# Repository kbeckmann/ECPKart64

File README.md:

# ECPKart64

A Lattice ECP5 based FPGA Flash Cart for the Nintendo 64

## Build and load over serial

```

# First install FPGA toolchain and LiteX

# Build and load stuff
make bitstream
make load_bitstream
make load_app

# Manually write "reboot" in the terminal, in order to trigger the upload of the app

# Upload a ROM
python -m gateware.ecpkart64.uploader2 --port /dev/ttyUSB1 --csr-csv csr.csv --cic --file myrom.z64

# Turn on power on the N64

```

## SD-Card

Currently this doesn't work properly for some reason (sd-card driver does not manage to interact with the card properly). But these are the steps normally taken:

```
# Build
make bitstream
make app

# Format and mount an SD-Card with FAT
sudo mkfs.vfat -F32 /dev/...
sudo mount /dev/... /mnt/usb

# Mount it and copy files to it
cp build/kilsyth/software/app/app.bin /mnt/usb/
cp rom.z64 /mnt/usb/

# Create boot.json with your configuration
echo '{
	"rom.z64":	0x40000000,
	"app.bin":	0x20000000
}' > /mnt/usb/boot.json

# Unmount, insert and boot. Turn on N64.

```

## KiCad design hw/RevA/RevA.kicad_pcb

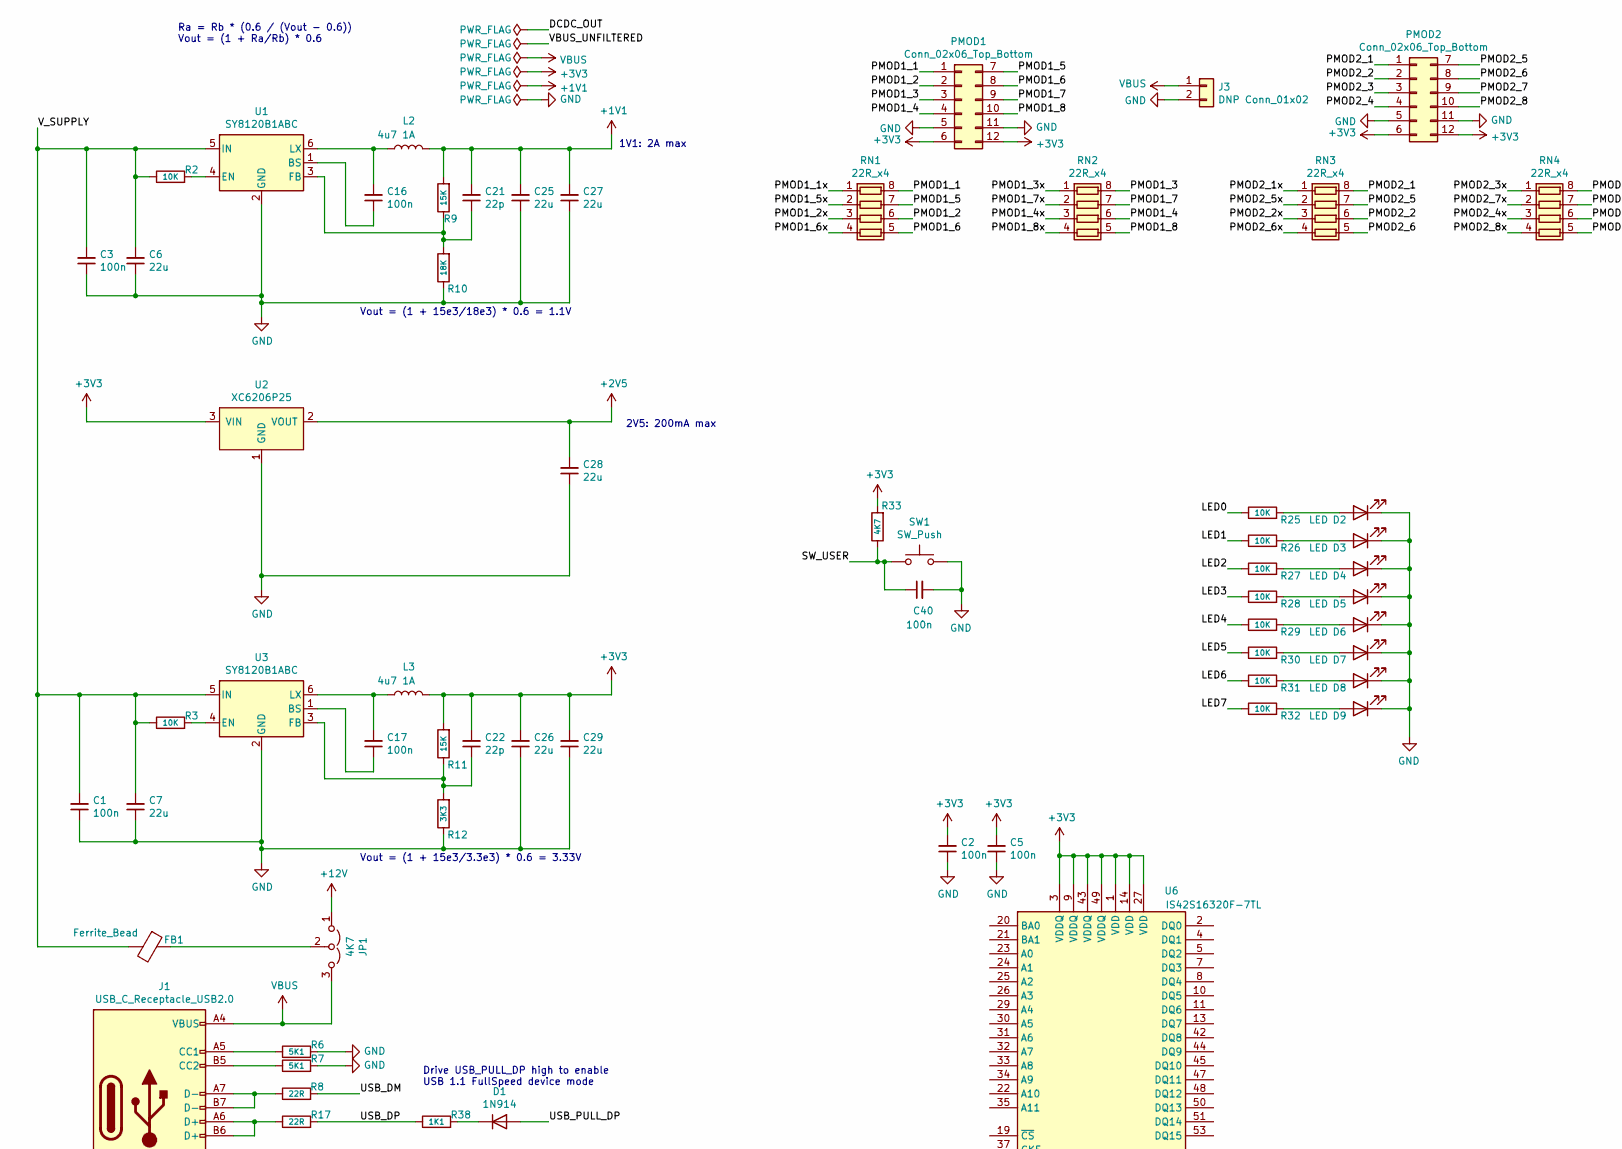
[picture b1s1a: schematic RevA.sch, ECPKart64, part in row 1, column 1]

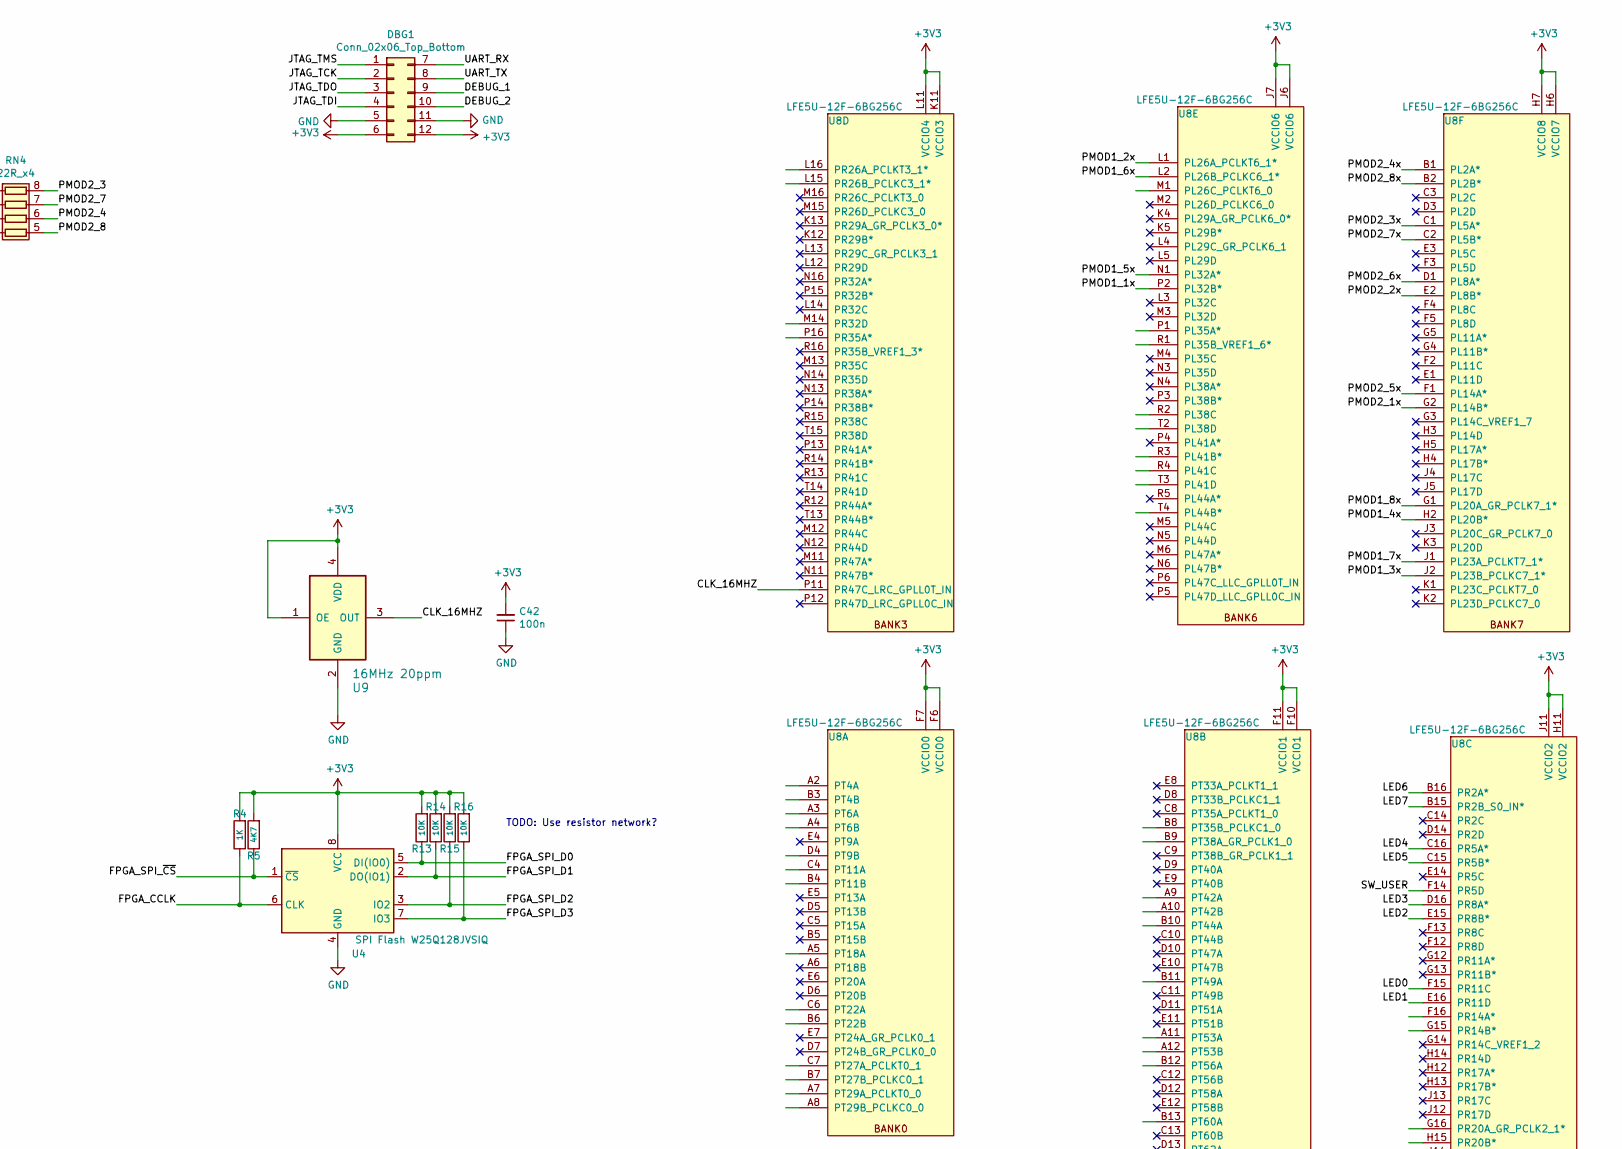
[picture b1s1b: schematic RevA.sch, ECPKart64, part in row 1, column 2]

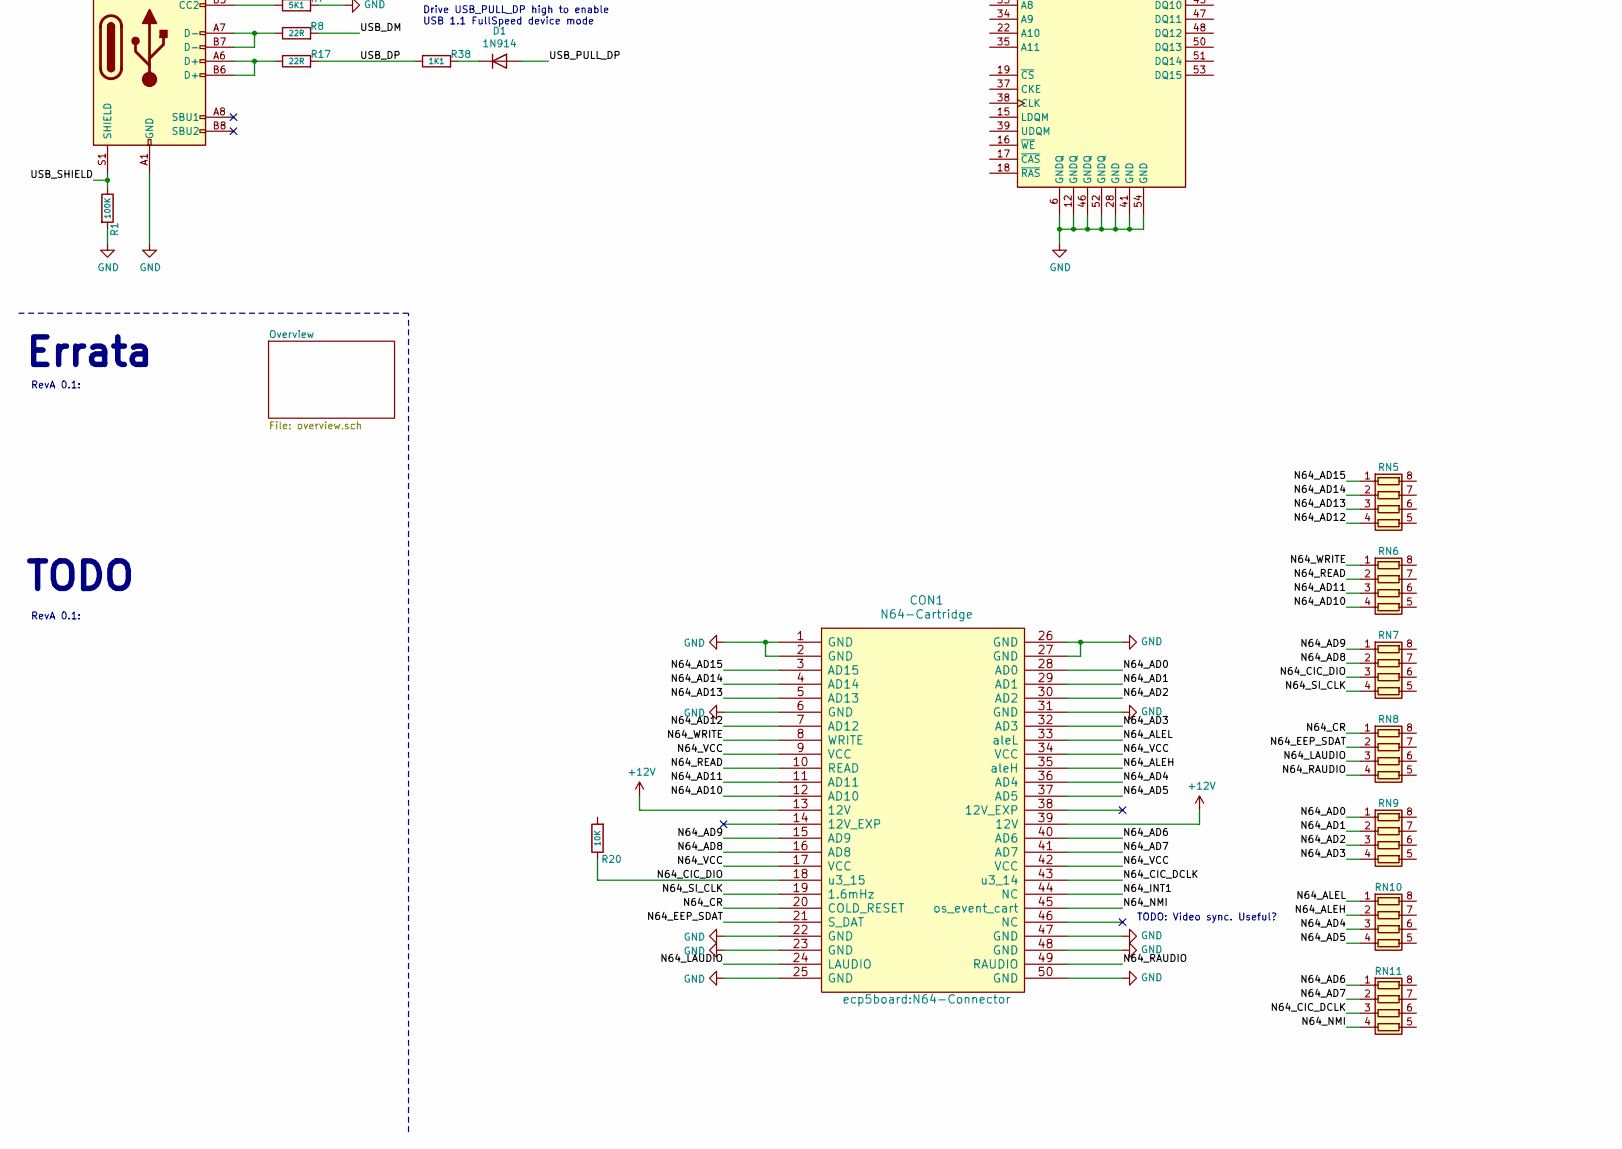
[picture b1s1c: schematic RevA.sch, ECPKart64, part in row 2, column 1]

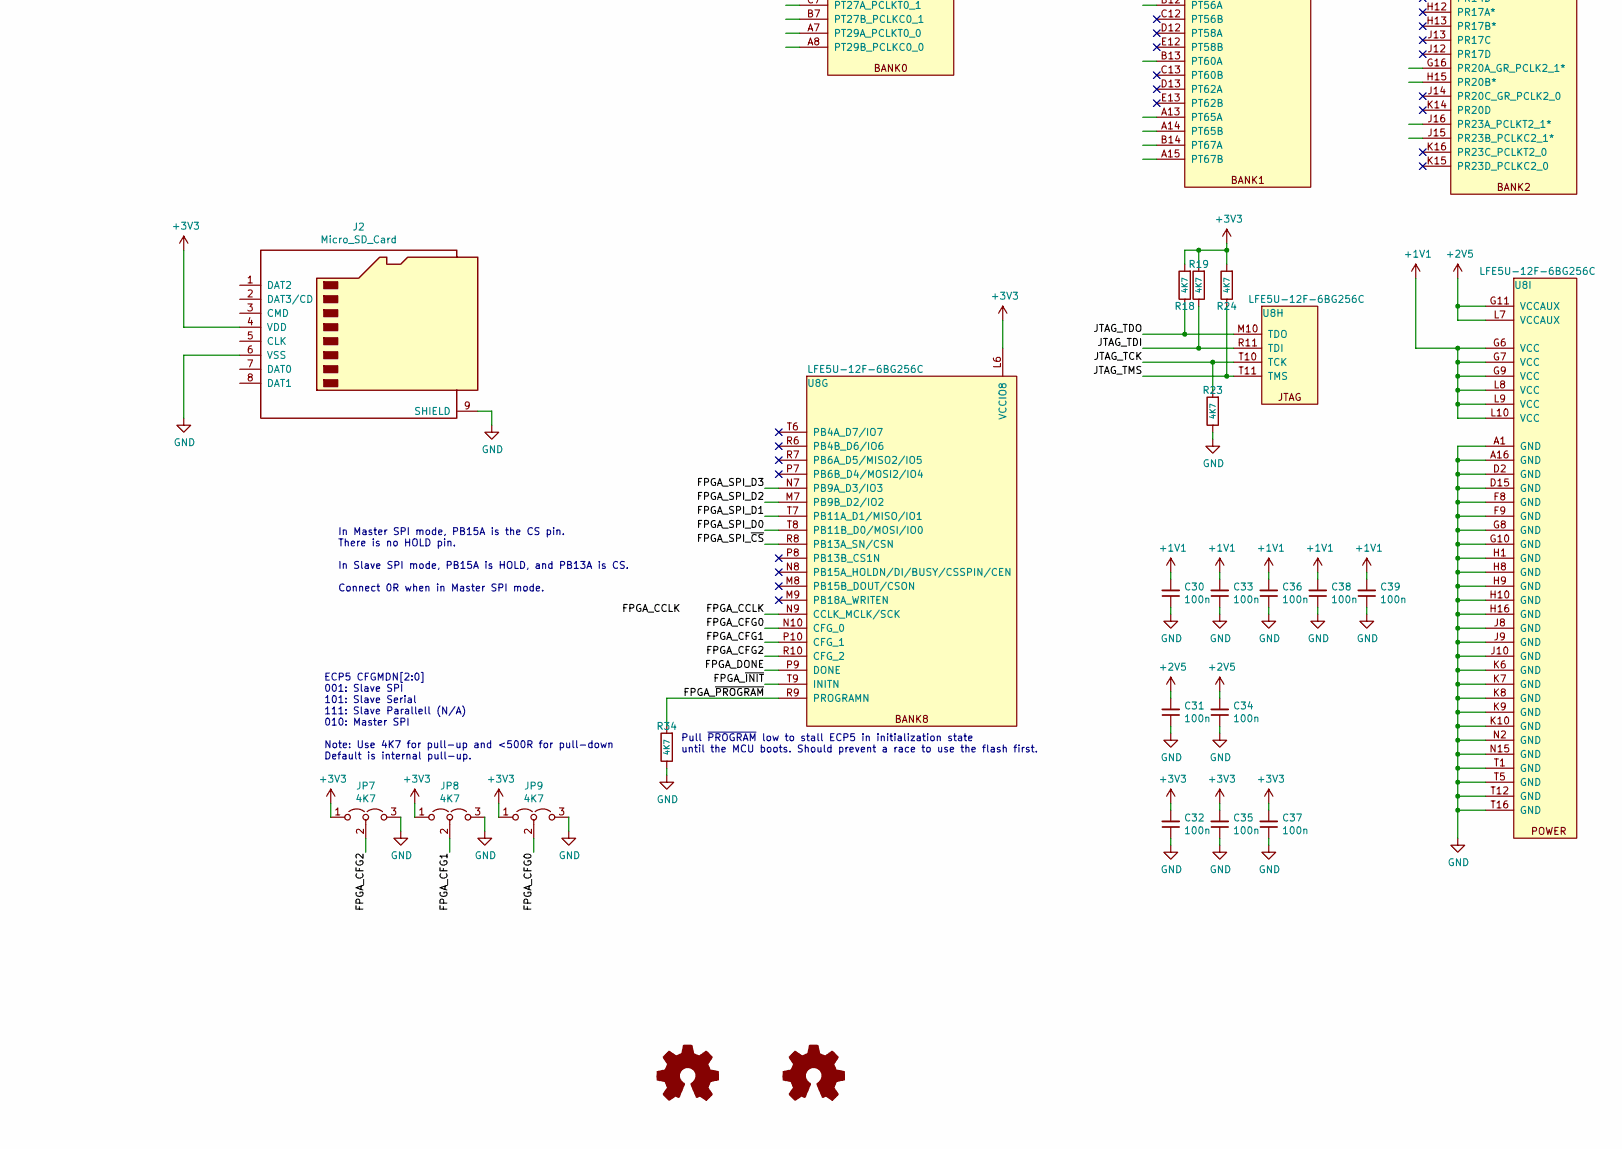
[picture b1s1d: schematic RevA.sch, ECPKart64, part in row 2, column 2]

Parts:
C1, C2, C3, C5, C16, C17, C30, C31, C32, C33, C34, C35, C36, C37, C38, C39, C40, C42: 100n; C_0402_1005Metric
C6, C7, C25, C26, C27, C28, C29: 22u; C_0805_2012Metric; LCSC C98190
C21, C22: 22p; C_0402_1005Metric
CON1: N64-Cartridge; N64-Connector
D1: 1N914; D_SOD-323_HandSoldering
D2, D3, D4, D5, D6, D7, D8, D9: LED; LED_0603_1608Metric; LCSC C84263
DBG1: Conn_02x06_Top_Bottom; PMOD_Socket_2x06_P2.54mm_Horizontal; LCSC C239357
FB1: Ferrite_Bead; L_0805_2012Metric; LCSC C88993
J1: USB_C_Receptacle_USB2.0; USB_C_Receptacle_GT-USB-7010; LCSC C165948
J2: Micro_SD_Card; microSD_HC_Molex_104031-0811
J3: DNP Conn_01x02; PinSocket_1x02_P2.54mm_Vertical
JP1: 4K7; PinHeader_1x03_P2.54mm_Horizontal; LCSC C105871
JP7, JP8, JP9: 4K7; JP_3_0402_1005Metric; LCSC C105871
L2, L3: 4u7 1A; L_1008_1210; LCSC C90319
LOGO1: Logo_Open_Hardware_Small; OSHW-Logo_5.7x6mm_SilkScreen
LOGO3: Logo_Open_Hardware_Small; xil_logo_new
PMOD1, PMOD2: Conn_02x06_Top_Bottom; PMOD_Socket_2x06_P2.54mm_Horizontal; LCSC C239357
R1: 100K; R_0402_1005Metric
R2, R3, R13, R14, R15, R16, R20, R25, R26, R27, R28, R29, R30, R31, R32: 10K; R_0402_1005Metric
R4: 1K; R_0402_1005Metric
R5, R18, R19, R23, R24, R33, R34: 4K7; R_0402_1005Metric
R6, R7: 5K1; R_0402_1005Metric
R8, R17: 22R; R_0402_1005Metric
R9, R11: 15K; R_0402_1005Metric
R10: 18K; R_0402_1005Metric
R12: 3K3; R_0402_1005Metric
R38: 1K1; R_0402_1005Metric
RN1, RN2, RN3, RN4, RN5, RN6, RN7, RN8, RN9, RN10, RN11: 22R_x4; R_Array_Convex_4x0603; LCSC C309446
SW1: SW_Push; SW_SPST_FSMSM; LCSC C118141
U1, U3: SY8120B1ABC; SOT-23-6; LCSC C88474
U2: XC6206P25; SOT-23; LCSC C15906
U4: SPI Flash W25Q128JVSIQ; SOA008-150-208mil; LCSC C97521
U6: IS42S16320F-7TL; TSOP-II-54_22.2x10.16mm_P0.8mm
U8: LFE5U-12F-6BG256C; cabga256; Mouser 842-LFE5U12F6BG256C
U9: 16MHz 20ppm; Crystal_SMD_3225-4Pin_3.2x2.5mm; LCSC C387369

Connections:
+1V1: C21.2, C25.2, C27.2, C30.2, C33.2, C36.2, C38.2, C39.2, L2.2, R9.2, U8.G6 (VCC), U8.G7 (VCC), U8.G9 (VCC), U8.L8 (VCC), U8.L9 (VCC), U8.L10 (VCC)
+2V5: C28.2, C31.2, C34.2, U2.2 (VOUT), U8.G11 (VCCAUX), U8.L7 (VCCAUX)
+3V3: C2.2, C5.2, C22.2, C26.2, C29.2, C32.2, C35.2, C37.2, C42.2, DBG1.6, DBG1.12, J2.4 (VDD), JP7.1 (A), JP8.1 (A), JP9.1 (A), L3.2, PMOD1.6, PMOD1.12, PMOD2.6, PMOD2.12, R4.2, R5.2, R11.2, R13.2, R14.2, R15.2, R16.2, R18.2, R19.2, R24.2, R33.2, U2.3 (VIN), U4.8 (VCC), U6.1 (VDD), U6.3 (VDDQ), U6.9 (VDDQ), U6.14 (VDD), U6.27 (VDD), U6.43 (VDDQ), U6.49 (VDDQ), U8.F6 (VCCIO0), U8.F7 (VCCIO0), U8.F10 (VCCIO1), U8.F11 (VCCIO1), U8.H6 (VCCIO7), U8.H7 (VCCIO8), U8.H11 (VCCIO2), U8.J6 (VCCIO6), U8.J7 (VCCIO6), U8.J11 (VCCIO2), U8.K11 (VCCIO3), U8.L6 (VCCIO8), U8.L11 (VCCIO4), U9.1 (OE), U9.4 (VDD)
+12V: CON1.13 (12V), CON1.39 (12V), JP1.1 (A)
/CLK_16MHZ: U8.P11 (PR47C_LRC_GPLL0T_IN), U9.3 (OUT)
/DEBUG_1: DBG1.9
/DEBUG_2: DBG1.10
/FPGA_CCLK: R4.1, U4.6 (CLK), U8.N9 (CCLK_MCLK/SCK)
/FPGA_CFG0: JP9.2 (C), U8.N10 (CFG_0)
/FPGA_CFG1: JP8.2 (C), U8.P10 (CFG_1)
/FPGA_CFG2: JP7.2 (C), U8.R10 (CFG_2)
/FPGA_DONE: U8.P9 (DONE)
/FPGA_SPI_D0: R13.1, U4.5 (DI(IO0)), U8.T8 (PB11B_D0/MOSI/IO0)
/FPGA_SPI_D1: R14.1, U4.2 (DO(IO1)), U8.T7 (PB11A_D1/MISO/IO1)
/FPGA_SPI_D2: R15.1, U4.3 (IO2), U8.M7 (PB9B_D2/IO2)
/FPGA_SPI_D3: R16.1, U4.7 (IO3), U8.N7 (PB9A_D3/IO3)
/FPGA_SPI_~CS~: R5.1, U4.1 (~CS), U8.R8 (PB13A_SN/CSN)
/FPGA_~INIT: U8.T9 (INITN)
/FPGA_~PROGRAM: R34.2, U8.R9 (PROGRAMN)
/JTAG_TCK: DBG1.2, R23.2, U8.T10 (TCK)
/JTAG_TDI: DBG1.4, R19.1, U8.R11 (TDI)
/JTAG_TDO: DBG1.3, R18.1, U8.M10 (TDO)
/JTAG_TMS: DBG1.1, R24.1, U8.T11 (TMS)
/LED0: R25.1, U8.F15 (PR11C)
/LED1: R26.1, U8.E16 (PR11D)
/LED2: R27.1, U8.E15 (PR8B*)
/LED3: R28.1, U8.D16 (PR8A*)
/LED4: R29.1, U8.C16 (PR5A*)
/LED5: R30.1, U8.C15 (PR5B*)
/LED6: R31.1, U8.B16 (PR2A*)
/LED7: R32.1, U8.B15 (PR2B_S0_IN*)
/N64_AD0: CON1.28 (AD0), RN9.1 (R1.1)
/N64_AD1: CON1.29 (AD1), RN9.2 (R2.1)
/N64_AD2: CON1.30 (AD2), RN9.3 (R3.1)
/N64_AD3: CON1.32 (AD3), RN9.4 (R4.1)
/N64_AD4: CON1.36 (AD4), RN10.3 (R3.1)
/N64_AD5: CON1.37 (AD5), RN10.4 (R4.1)
/N64_AD6: CON1.40 (AD6), RN11.1 (R1.1)
/N64_AD7: CON1.41 (AD7), RN11.2 (R2.1)
/N64_AD8: CON1.16 (AD8), RN7.2 (R2.1)
/N64_AD9: CON1.15 (AD9), RN7.1 (R1.1)
/N64_AD10: CON1.12 (AD10), RN6.4 (R4.1)
/N64_AD11: CON1.11 (AD11), RN6.3 (R3.1)
/N64_AD12: CON1.7 (AD12), RN5.4 (R4.1)
/N64_AD13: CON1.5 (AD13), RN5.3 (R3.1)
/N64_AD14: CON1.4 (AD14), RN5.2 (R2.1)
/N64_AD15: CON1.3 (AD15), RN5.1 (R1.1)
/N64_ALEH: CON1.35 (aleH), RN10.2 (R2.1)
/N64_ALEL: CON1.33 (aleL), RN10.1 (R1.1)
/N64_CIC_DCLK: CON1.43 (u3_14), RN11.3 (R3.1)
/N64_CIC_DIO: CON1.18 (u3_15), R20.1, RN7.3 (R3.1)
/N64_CR: CON1.20 (COLD_RESET), RN8.1 (R1.1)
/N64_EEP_SDAT: CON1.21 (S_DAT), RN8.2 (R2.1)
/N64_INT1: CON1.44 (NC)
/N64_LAUDIO: CON1.24 (LAUDIO), RN8.3 (R3.1)
/N64_NMI: CON1.45 (os_event_cart), RN11.4 (R4.1)
/N64_RAUDIO: CON1.49 (RAUDIO), RN8.4 (R4.1)
/N64_READ: CON1.10 (READ), RN6.2 (R2.1)
/N64_SI_CLK: CON1.19 (1.6mHz), RN7.4 (R4.1)
/N64_VCC: CON1.9 (VCC), CON1.17 (VCC), CON1.34 (VCC), CON1.42 (VCC)
/N64_WRITE: CON1.8 (WRITE), RN6.1 (R1.1)
/PMOD1_1: PMOD1.1, RN1.8 (R1.2)
/PMOD1_1x: RN1.1 (R1.1), U8.P2 (PL32B*)
/PMOD1_2: PMOD1.2, RN1.6 (R3.2)
/PMOD1_2x: RN1.3 (R3.1), U8.L1 (PL26A_PCLKT6_1*)
/PMOD1_3: PMOD1.3, RN2.8 (R1.2)
/PMOD1_3x: RN2.1 (R1.1), U8.J2 (PL23B_PCLKC7_1*)
/PMOD1_4: PMOD1.4, RN2.6 (R3.2)
/PMOD1_4x: RN2.3 (R3.1), U8.H2 (PL20B*)
/PMOD1_5: PMOD1.7, RN1.7 (R2.2)
/PMOD1_5x: RN1.2 (R2.1), U8.N1 (PL32A*)
/PMOD1_6: PMOD1.8, RN1.5 (R4.2)
/PMOD1_6x: RN1.4 (R4.1), U8.L2 (PL26B_PCLKC6_1*)
/PMOD1_7: PMOD1.9, RN2.7 (R2.2)
/PMOD1_7x: RN2.2 (R2.1), U8.J1 (PL23A_PCLKT7_1*)
/PMOD1_8: PMOD1.10, RN2.5 (R4.2)
/PMOD1_8x: RN2.4 (R4.1), U8.G1 (PL20A_GR_PCLK7_1*)
/PMOD2_1: PMOD2.1, RN3.8 (R1.2)
/PMOD2_1x: RN3.1 (R1.1), U8.G2 (PL14B*)
/PMOD2_2: PMOD2.2, RN3.6 (R3.2)
/PMOD2_2x: RN3.3 (R3.1), U8.E2 (PL8B*)
/PMOD2_3: PMOD2.3, RN4.8 (R1.2)
/PMOD2_3x: RN4.1 (R1.1), U8.C1 (PL5A*)
/PMOD2_4: PMOD2.4, RN4.6 (R3.2)
/PMOD2_4x: RN4.3 (R3.1), U8.B1 (PL2A*)
/PMOD2_5: PMOD2.7, RN3.7 (R2.2)
/PMOD2_5x: RN3.2 (R2.1), U8.F1 (PL14A*)
/PMOD2_6: PMOD2.8, RN3.5 (R4.2)
/PMOD2_6x: RN3.4 (R4.1), U8.D1 (PL8A*)
/PMOD2_7: PMOD2.9, RN4.7 (R2.2)
/PMOD2_7x: RN4.2 (R2.1), U8.C2 (PL5B*)
/PMOD2_8: PMOD2.10, RN4.5 (R4.2)
/PMOD2_8x: RN4.4 (R4.1), U8.B2 (PL2B*)
/SW_USER: C40.1, R33.1, SW1.1, U8.F14 (PR5D)
/UART_RX: DBG1.7
/UART_TX: DBG1.8
/USB_DM: R8.2
/USB_DP: R17.2, R38.1
/USB_PULL_DP: D1.2 (A)
/USB_SHIELD: J1.S1 (SHIELD), R1.1
/V_SUPPLY: C1.2, C3.2, C6.2, C7.2, FB1.2, R2.1, R3.1, U1.5 (IN), U3.5 (IN)
GND: C1.1, C2.1, C3.1, C5.1, C6.1, C7.1, C25.1, C26.1, C27.1, C28.1, C29.1, C30.1, C31.1, C32.1, C33.1, C34.1, C35.1, C36.1, C37.1, C38.1, C39.1, C40.2, C42.1, CON1.1 (GND), CON1.2 (GND), CON1.6 (GND), CON1.22 (GND), CON1.23 (GND), CON1.25 (GND), CON1.26 (GND), CON1.27 (GND), CON1.31 (GND), CON1.47 (GND), CON1.48 (GND), CON1.50 (GND), D2.1 (K), D3.1 (K), D4.1 (K), D5.1 (K), D6.1 (K), D7.1 (K), D8.1 (K), D9.1 (K), DBG1.5, DBG1.11, J1.A1 (GND), J1.A12 (GND), J1.B1 (GND), J1.B12 (GND), J2.6 (VSS), J2.9 (SHIELD), J3.2, JP7.3 (B), JP8.3 (B), JP9.3 (B), PMOD1.5, PMOD1.11, PMOD2.5, PMOD2.11, R1.2, R6.2, R7.2, R10.1, R12.1, R23.1, R34.1, SW1.2, U1.2 (GND), U2.1 (GND), U3.2 (GND), U4.4 (GND), U6.6 (GNDQ), U6.12 (GNDQ), U6.28 (GND), U6.41 (GND), U6.46 (GNDQ), U6.52 (GNDQ), U6.54 (GND), U8.A1 (GND), U8.A16 (GND), U8.D2 (GND), U8.D15 (GND), U8.F8 (GND), U8.F9 (GND), U8.G8 (GND), U8.G10 (GND), U8.H1 (GND), U8.H8 (GND), U8.H9 (GND), U8.H10 (GND), U8.H16 (GND), U8.J8 (GND), U8.J9 (GND), U8.J10 (GND), U8.K6 (GND), U8.K7 (GND), U8.K8 (GND), U8.K9 (GND), U8.K10 (GND), U8.N2 (GND), U8.N15 (GND), U8.T1 (GND), U8.T5 (GND), U8.T12 (GND), U8.T16 (GND), U9.2 (GND)
unnamed: C16.1, U1.1 (BS)
unnamed: C16.2, L2.1, U1.6 (LX)
unnamed: C17.1, U3.1 (BS)
unnamed: C17.2, L3.1, U3.6 (LX)
unnamed: C21.1, R9.1, R10.2, U1.3 (FB)
unnamed: C22.1, R11.1, R12.2, U3.3 (FB)
unnamed: D1.1 (K), R38.2
unnamed: D2.2 (A), R25.2
unnamed: D3.2 (A), R26.2
unnamed: D4.2 (A), R27.2
unnamed: D5.2 (A), R28.2
unnamed: D6.2 (A), R29.2
unnamed: D7.2 (A), R30.2
unnamed: D8.2 (A), R31.2
unnamed: D9.2 (A), R32.2
unnamed: FB1.1, JP1.2 (C)
unnamed: J1.A5 (CC1), R6.1
unnamed: J1.A6 (D+), J1.B6 (D+), R17.1
unnamed: J1.A7 (D-), J1.B7 (D-), R8.1
unnamed: J1.B5 (CC2), R7.1
unnamed: R2.2, U1.4 (EN)
unnamed: R3.2, U3.4 (EN)
VBUS: J1.A4 (VBUS), J1.A9 (VBUS), J1.B4 (VBUS), J1.B9 (VBUS), J3.1, JP1.3 (B)

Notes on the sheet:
Ra = Rb * (0.6 / (Vout - 0.6)) Vout = (1 + Ra/Rb) * 0.6
Vout = (1 + 15e3/18e3) * 0.6 = 1.1V
2V5: 200mA max
1V1: 2A max
Vout = (1 + 15e3/3.3e3) * 0.6 = 3.33V
ECP5 CFGMDN[2:0] 001: Slave SPI 101: Slave Serial 111: Slave Parallell (N/A) 010: Master SPI Note: Use 4K7 for pull-up and <500R for pull-down Default is internal pull-up.
Pull ~PROGRAM~ low to stall ECP5 in initialization state until the MCU boots. Should prevent a race to use the flash first.
In Master SPI mode, PB15A is the CS pin. There is no HOLD pin. In Slave SPI mode, PB15A is HOLD, and PB13A is CS. Connect 0R when in Master SPI mode.
Errata
RevA 0.1:
TODO
Drive USB_PULL_DP high to enable USB 1.1 FullSpeed device mode
TODO: Video sync. Useful?
TODO: Use resistor network?

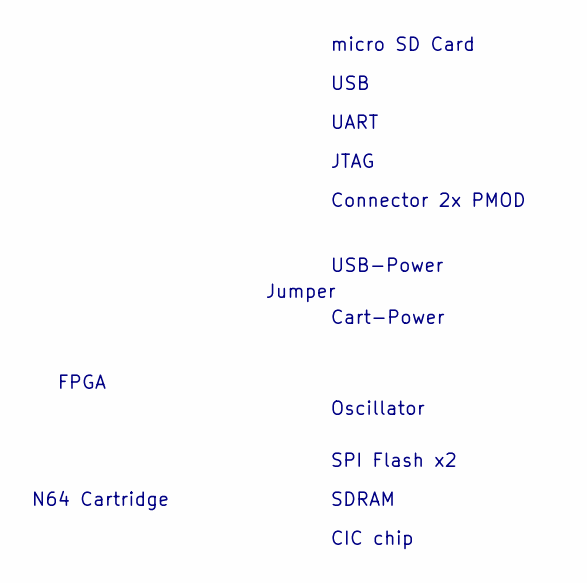
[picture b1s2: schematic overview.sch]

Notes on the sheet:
N64 Cartridge
FPGA
SDRAM
SPI Flash x2
USB
micro SD Card
UART
JTAG
Cart-Power
USB-Power
Jumper
Oscillator
Connector 2x PMOD
CIC chip

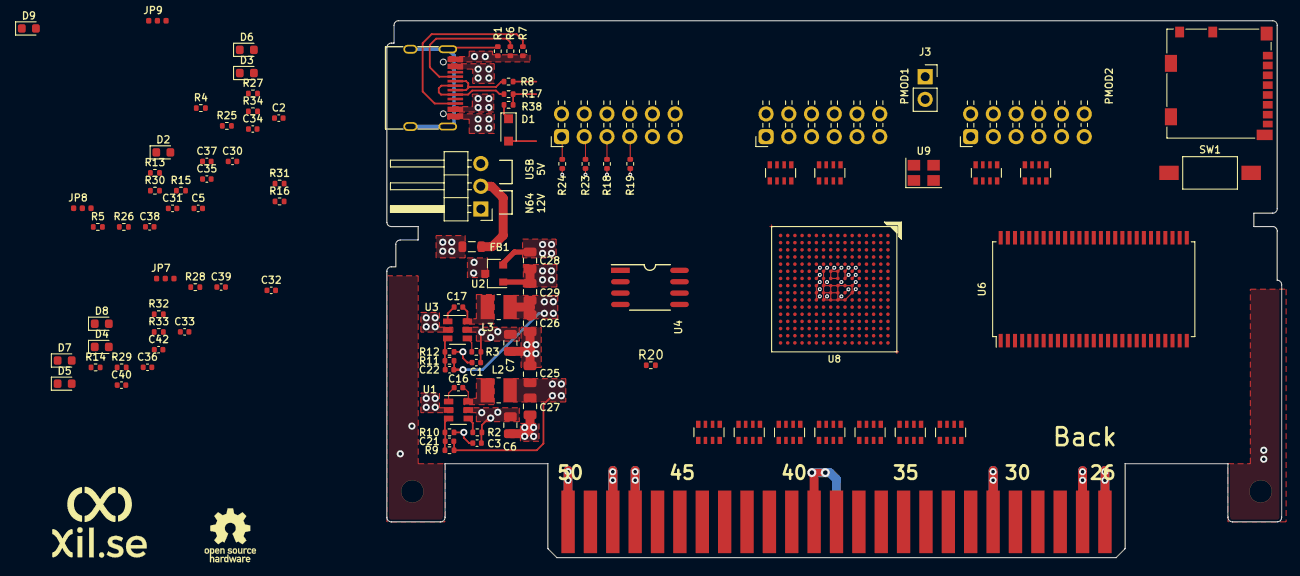
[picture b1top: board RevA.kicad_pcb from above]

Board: 4 copper layers, 100.0 x 60.0 mm, 104 parts (1 on the bottom side), 116 nets.

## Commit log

2021-08-16 Fork Pergola
2021-08-16 Progress
2021-08-16 Import pcb shape
2021-08-17 size
2021-08-27 Add initial gateware bringup using Kilsyth
2021-08-27 Add basic application
2021-08-27 Add root level Makefile
2021-08-27 CIC: Add early port (probably broken)
2021-08-27 Add CI
2021-08-27 ci stuff
2021-08-28 worksish!
2021-08-28 Progress!!
2021-08-29 Improve stuff perhaps
2021-08-29 Improve debug tooling and split up the code a bit
2021-08-29 Optionally read bootrom
2021-08-29 Fix stuff
2021-08-29 Boot continues further now
2021-08-29 improve logging
2021-08-29 It boots!!!
2021-08-29 Log the first 4096 rom accesses
2021-08-29 Fix makefile
2021-08-29 Fix makefile some more
2021-08-30 Fetch from SDRAM (not working properly yet)
2021-08-30 Add dedicated bus to the SDRAM for the n64 module
2021-08-30 Use native SDRAM port
2021-08-31 Log SDRAM access times
2021-08-31 Match new memory area name
2021-08-31 Add SDCard support
2021-08-31 Add workaround for slow SDRAM latency
2021-08-31 Fix incorrect comment
2021-09-01 Add more features in the app
2021-09-01 Use more conservative read strobe configuration
2021-09-01 Ignore more junk
2021-09-02 Configurable baudrate
2021-09-03 cic: Exit the CIC app on any uart input
2021-09-03 cic: Exit when reset is detected
2021-09-03 Prepare for SDCard code
2021-09-03 Make the first ROM word configurable
2021-09-03 Add USB pins on PMOD
2021-09-03 cic: Improve reset logic
2021-09-04 add boot trace
2021-09-04 Improve SDRAM latency by halting refresh during reads
2021-09-04 Improve latency
2021-09-05 Start cic automatically
2021-09-05 hw: Progress
    - Added pullup resistor for CIC data
    - Removed extra SPI flash (no need for it anymore)
    - Rounded corners
2021-09-05 cic: Print less to start faster
2021-09-05 Clean up analyzed signals
2021-09-05 Cleanup
2021-09-05 cic: Remove print after reset
2021-09-09 Improvements
    - Add optional USB support
    - Refactor cart code
    - Add a video generator in gateware
2021-09-09 Use standard header
2021-09-09 Map video generator to SRAM address space
2021-09-21 Save build logs
2022-03-25 Fix CI
2022-03-25 aaaaaaaa
2022-03-25 aaa?
2022-03-25 aaaaa
2022-03-25 aaaaaaaaaaa
2022-03-25 aaaAAaAAAa
2022-03-25 AaAAAAAAAAAAAAAaaaaaaaaaaaa
2022-03-26 Update to latest LiteX
2022-03-26 Add progress bar
2022-03-26 Improve docs
2022-03-26 Add dump_mem.py
2022-03-26 Rename to dump_logger.py
2022-03-27 Add write support (WIP)
2022-03-27 Support dump to file
2022-03-27 Add framebuffer dumper
2022-03-27 Update license
2022-04-16 mailbox: Initial implementation
    To be used for communication between a program on the N64 and a host PC. See runner.py for a ping/pong example.
2022-04-16 cic: Exit by sending \n
2022-04-21 cart: Only set sdram_wait.eq(0) when accessing SDRAM
    I have run Super Mario 64 over the night without getting any bit errors, so seems fine.
2022-04-21 runner: Implement runner and commander
    Read/write/execute on the N64 itself
